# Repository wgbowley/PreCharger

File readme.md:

### Pre-Charger circuit (recruit project)

Thank you for checking out my "side quest" into high voltage prechargers. It was generally a joy, and the elegance of some of these designs is truly exceptional. 
I had never really considered HV as a possible domain of exploration. However, after breaking down this problem, or more specifically the need for either active or passive chargers, that changed.
I have come to appreciate the idiosyncrasies of the domain, and honestly, it really was quite a pleasure. I have not validated or checked my work within this repo due to time constraints from other commitments, 
but feel free to reach out if I made a horrendous leap in judgment (probably due to bad assumptions).

Funny enough, I did not want to be highly abstract with this project. But when I was playing around with schematics in my notebook, 
I thought, "Holy! I can use this for version 2 of the coil launcher" because it needs a constant current or a passive pre-charger.
Man, I love abstractions. Nevertheless, thank you for reading, and I hope you find the work here useful.

# Credits:

### Research & Development Enabled by:
* [Texas instruments](https://www.ti.com/) - Thank you. That floating reference logic is literally so eloquent. I was smiling from ear to ear when I understood it.
* [RMIT RACE TEAM](https://www.rmitmotorsport.com/) - Generally, independent of the outcome of my time as a recruit, this was quite uplifting compared to motor design.

### Bibtex Citation:

```
@misc{Bowley_2026,
  author = {Bowley, William},
  title = {{PreCharger}},
  url = {https://github.com/wgbowley/PreCharger},
  year = {2026},
  note = {GitHub repository},
  license = {MIT}
}
```

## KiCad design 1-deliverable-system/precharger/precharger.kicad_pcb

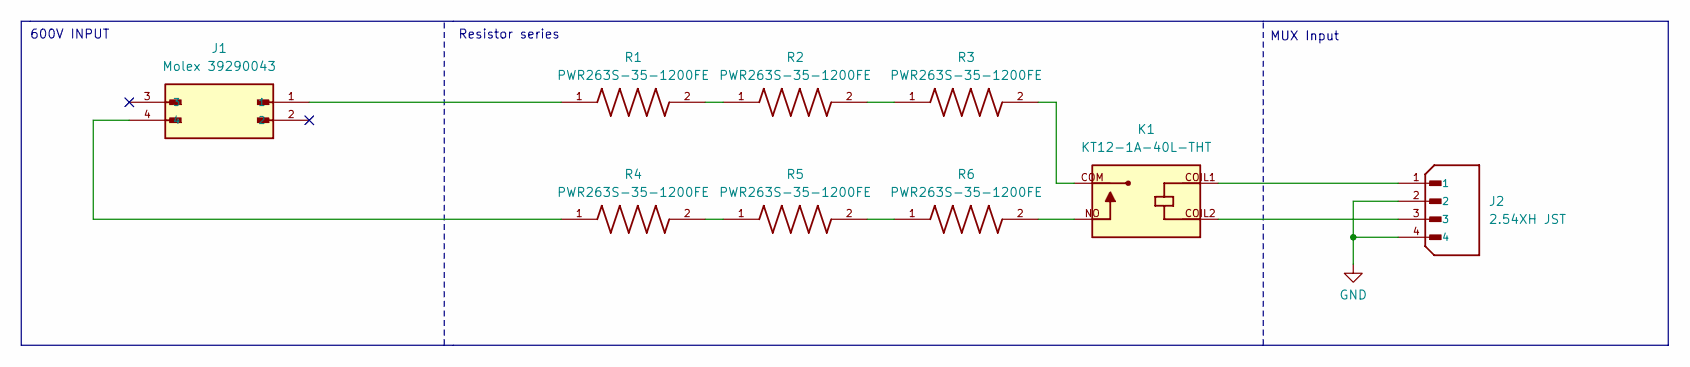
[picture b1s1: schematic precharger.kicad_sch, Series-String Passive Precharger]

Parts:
J1: Molex 39290043; MOLEX_39290043; PARTREV M4
J2: 2.54XH JST; JST_B4B-XH-A_LF__SN_; PARTREV 7/4/21
K1: KT12-1A-40L-THT; RELAY_KT12-1A-40L-THT; PARTREV 9
R1, R2, R3, R4, R5, R6: PWR263S-35-1200FE; RES_PWR263S-35-1200FE; PARTREV 12/20

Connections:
GND: J2.2, J2.4
unnamed: J1.1, R1.1
unnamed: J1.4, R4.1
unnamed: J2.1, K1.COIL1
unnamed: J2.3, K1.COIL2
unnamed: K1.COM, R3.2
unnamed: K1.NO, R6.2
unnamed: R1.2, R2.1
unnamed: R2.2, R3.1
unnamed: R4.2, R5.1
unnamed: R5.2, R6.1

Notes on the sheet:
600V INPUT
Resistor series
MUX Input

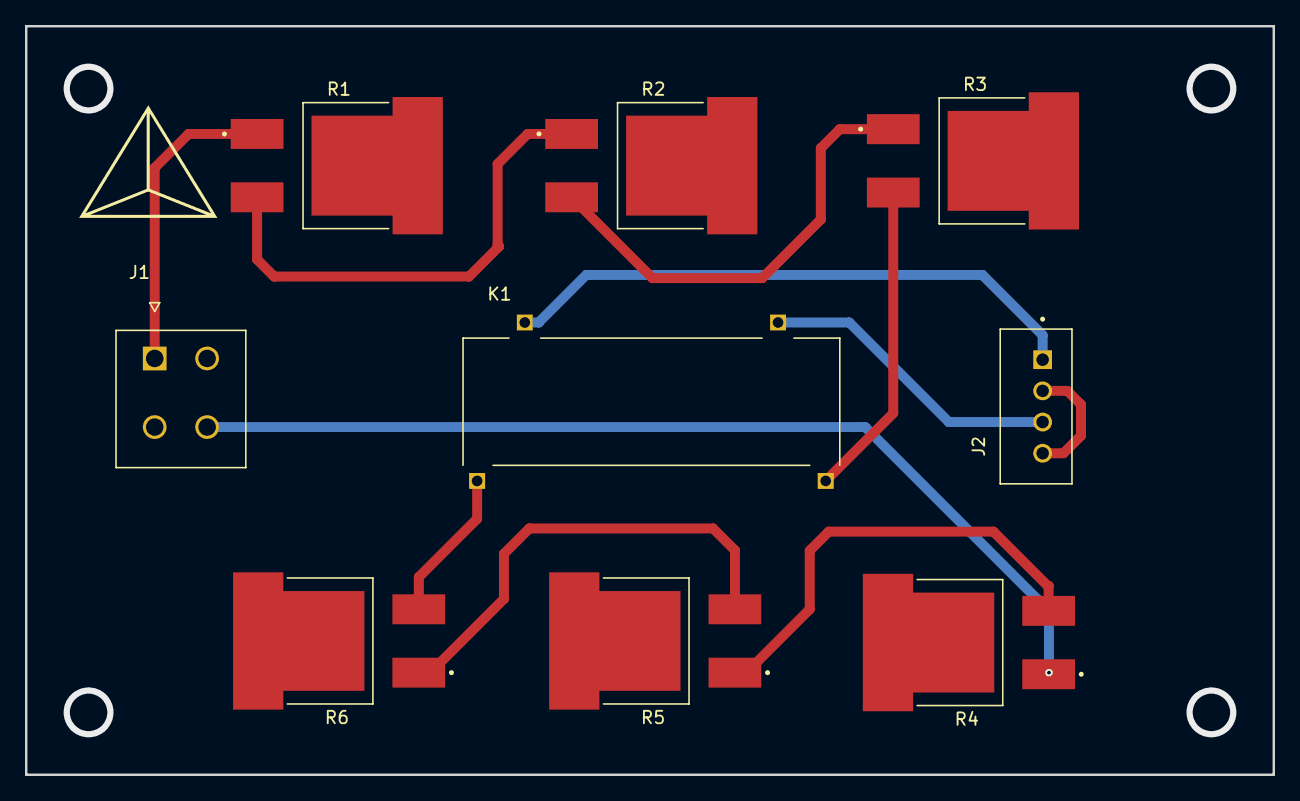
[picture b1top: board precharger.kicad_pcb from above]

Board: 2 copper layers, 100.0 x 60.0 mm, 9 parts (0 on the bottom side), 11 nets.

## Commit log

2026-03-31 initial work. Initial research.
2026-04-12 initial design exploration
2026-04-12 simulation with floating refer & import of rules
2026-04-12 made a prototype lumped parameter simulation for better control of variables
2026-04-13 analytical model for active charger - finished
2026-04-13 stress function as optimization vector
2026-04-13 passive vs active (quick save)
2026-04-14 laptop work (wip - passive)
2026-04-14 simulation + scaling laws finished -> detailed design started
2026-04-15 detailed designed started + ltspice simulation WIP
2026-04-15 why does ltspice not want to work :/
2026-04-16 got damn it .log and .op ltspice why?? not put them in .asc
2026-04-16 Why did TI have a direct reference to net 0 :/ | last updates before recruit project deadline (internally)
2026-04-16 write up & sign off :✌️:
    Plz be right
2026-04-16 damn don't copy and paste.
2026-04-16 structural change + series-string passive pre charger
2026-04-17 rough pcb design
